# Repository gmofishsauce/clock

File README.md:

# Nixie tube clock with WiFi

This is a Nixie tube clock with IN-12 (axial view) Nixie tubes.
For nice packaging, the design is split into two boards. They
mount [at right angles](https://docs.google.com/presentation/d/11yNopbXGtAtQ4xKlA-b-B579JGvuL5Y8hJCB-doAy8I/edit?usp=sharing) using 96-pin Eurobus ("VME") connectors.

## Subdirectories:

- logic: logic (base board) with Arduino, drivers, power supply.
- display: display board with Nixie tube sockets
- proto: a prototype to check out the PCB footprints.

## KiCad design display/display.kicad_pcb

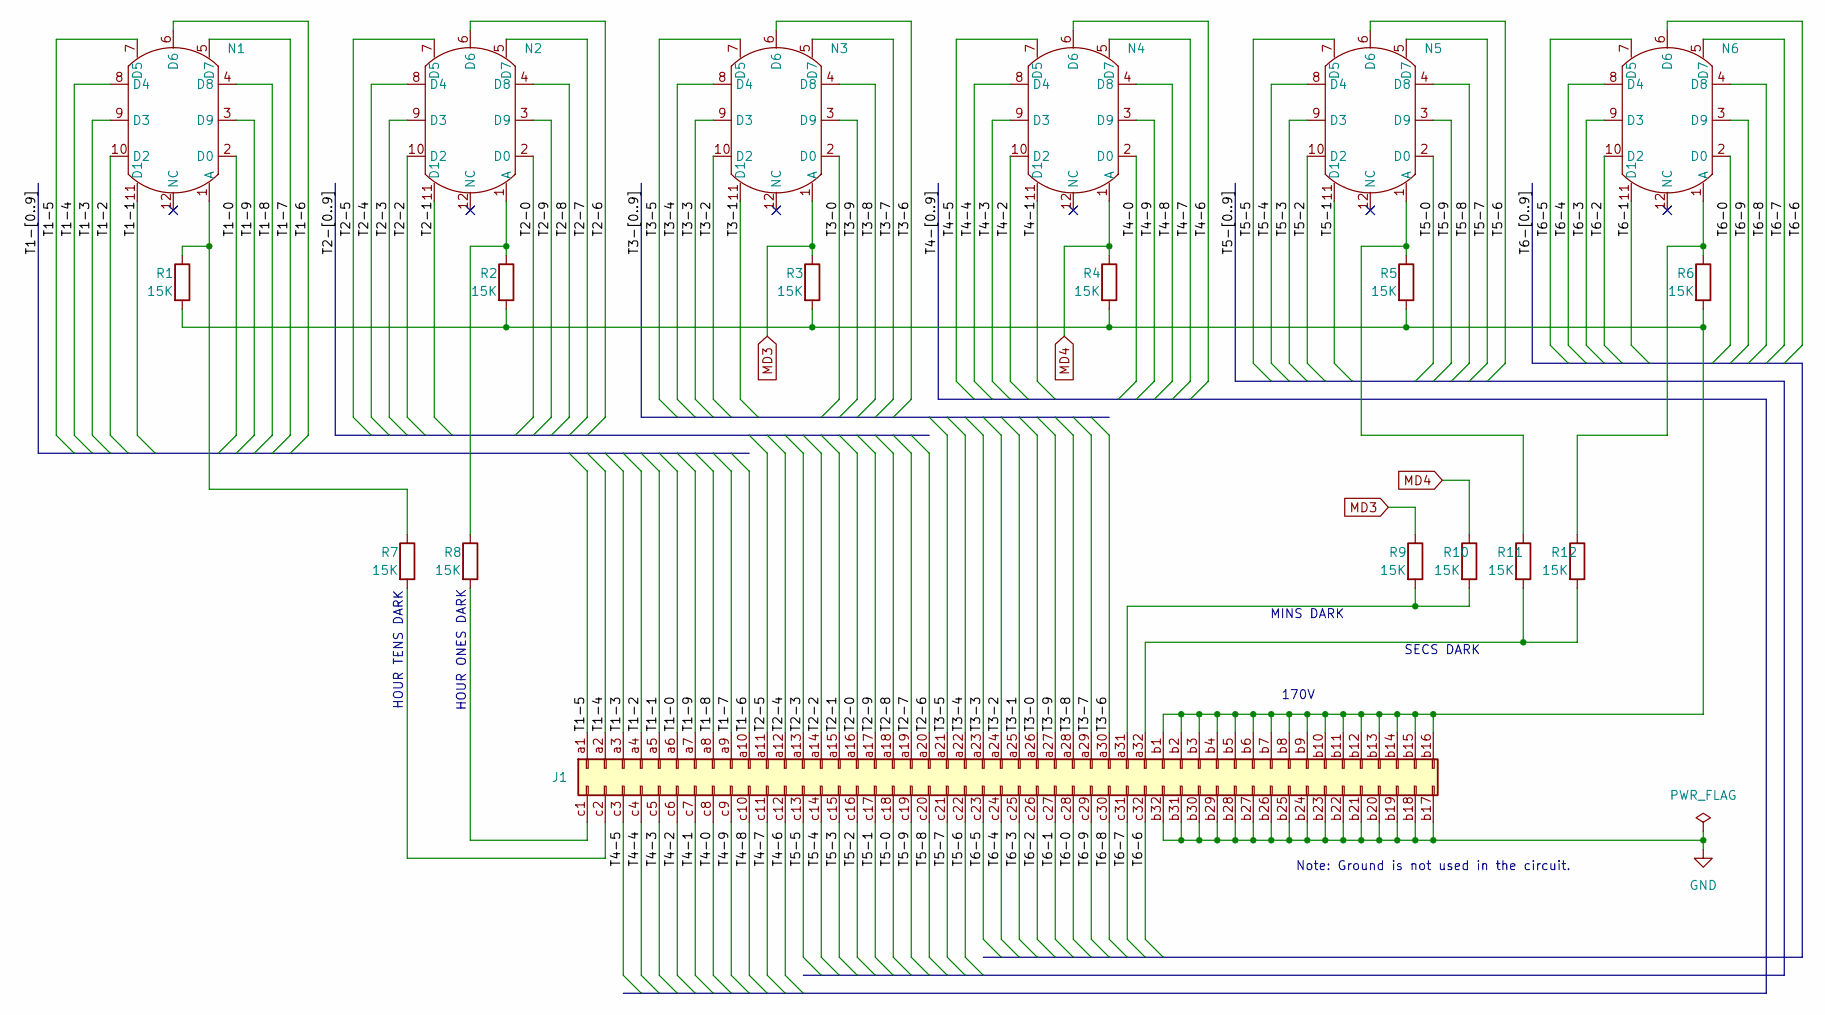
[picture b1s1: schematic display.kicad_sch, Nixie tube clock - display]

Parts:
J1: DIN41612_03x32_ABC; DIN41612_R_3x32_Female_Horizontal_THT
N1, N2, N3, N4, N5, N6: IN_12B_Socket
R1, R2, R3, R4, R5, R6, R7, R8, R9, R10, R11, R12: 15K; R_Box_L13.0mm_W4.0mm_P9.00mm

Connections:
/T1-0: J1.a6, N1.2 (D0)
/T1-1: J1.a5, N1.11 (D1)
/T1-2: J1.a4, N1.10 (D2)
/T1-3: J1.a3, N1.9 (D3)
/T1-4: J1.a2, N1.8 (D4)
/T1-5: J1.a1, N1.7 (D5)
/T1-6: J1.a10, N1.6 (D6)
/T1-7: J1.a9, N1.5 (D7)
/T1-8: J1.a8, N1.4 (D8)
/T1-9: J1.a7, N1.3 (D9)
/T2-0: J1.a16, N2.2 (D0)
/T2-1: J1.a15, N2.11 (D1)
/T2-2: J1.a14, N2.10 (D2)
/T2-3: J1.a13, N2.9 (D3)
/T2-4: J1.a12, N2.8 (D4)
/T2-5: J1.a11, N2.7 (D5)
/T2-6: J1.a20, N2.6 (D6)
/T2-7: J1.a19, N2.5 (D7)
/T2-8: J1.a18, N2.4 (D8)
/T2-9: J1.a17, N2.3 (D9)
/T3-0: J1.a26, N3.2 (D0)
/T3-1: J1.a25, N3.11 (D1)
/T3-2: J1.a24, N3.10 (D2)
/T3-3: J1.a23, N3.9 (D3)
/T3-4: J1.a22, N3.8 (D4)
/T3-5: J1.a21, N3.7 (D5)
/T3-6: J1.a30, N3.6 (D6)
/T3-7: J1.a29, N3.5 (D7)
/T3-8: J1.a28, N3.4 (D8)
/T3-9: J1.a27, N3.3 (D9)
/T4-0: J1.c8, N4.2 (D0)
/T4-1: J1.c7, N4.11 (D1)
/T4-2: J1.c6, N4.10 (D2)
/T4-3: J1.c5, N4.9 (D3)
/T4-4: J1.c4, N4.8 (D4)
/T4-5: J1.c3, N4.7 (D5)
/T4-6: J1.c12, N4.6 (D6)
/T4-7: J1.c11, N4.5 (D7)
/T4-8: J1.c10, N4.4 (D8)
/T4-9: J1.c9, N4.3 (D9)
/T5-0: J1.c18, N5.2 (D0)
/T5-1: J1.c17, N5.11 (D1)
/T5-2: J1.c16, N5.10 (D2)
/T5-3: J1.c15, N5.9 (D3)
/T5-4: J1.c14, N5.8 (D4)
/T5-5: J1.c13, N5.7 (D5)
/T5-6: J1.c22, N5.6 (D6)
/T5-7: J1.c21, N5.5 (D7)
/T5-8: J1.c20, N5.4 (D8)
/T5-9: J1.c19, N5.3 (D9)
/T6-0: J1.c28, N6.2 (D0)
/T6-1: J1.c27, N6.11 (D1)
/T6-2: J1.c26, N6.10 (D2)
/T6-3: J1.c25, N6.9 (D3)
/T6-4: J1.c24, N6.8 (D4)
/T6-5: J1.c23, N6.7 (D5)
/T6-6: J1.c32, N6.6 (D6)
/T6-7: J1.c31, N6.5 (D7)
/T6-8: J1.c30, N6.4 (D8)
/T6-9: J1.c29, N6.3 (D9)
GND: J1.b17, J1.b18, J1.b19, J1.b20, J1.b21, J1.b22, J1.b23, J1.b24, J1.b25, J1.b26, J1.b27, J1.b28, J1.b29, J1.b30, J1.b31, J1.b32
MD3: N3.1 (A), R3.1, R9.1
MD4: N4.1 (A), R4.1, R10.1
unnamed: J1.a31, R9.2, R10.2
unnamed: J1.a32, R11.2, R12.2
unnamed: J1.b1, J1.b2, J1.b3, J1.b4, J1.b5, J1.b6, J1.b7, J1.b8, J1.b9, J1.b10, J1.b11, J1.b12, J1.b13, J1.b14, J1.b15, J1.b16, R1.2, R2.2, R3.2, R4.2, R5.2, R6.2
unnamed: J1.c1, R8.2
unnamed: J1.c2, R7.2
unnamed: N1.1 (A), R1.1, R7.1
unnamed: N2.1 (A), R2.1, R8.1
unnamed: N5.1 (A), R5.1, R11.1
unnamed: N6.1 (A), R6.1, R12.1

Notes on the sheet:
Note: Ground is not used in the circuit.
MINS DARK
SECS DARK
HOUR ONES DARK
170V
HOUR TENS DARK

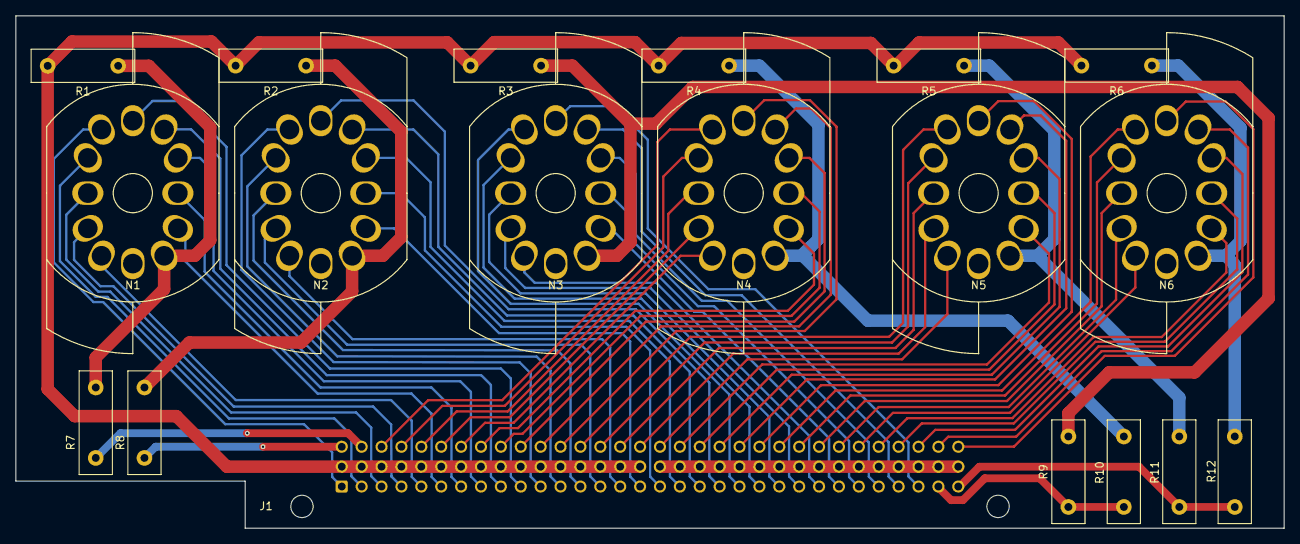
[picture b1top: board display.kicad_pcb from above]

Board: 4 copper layers, 162.0 x 65.4 mm, 19 parts (1 on the bottom side), 72 nets.

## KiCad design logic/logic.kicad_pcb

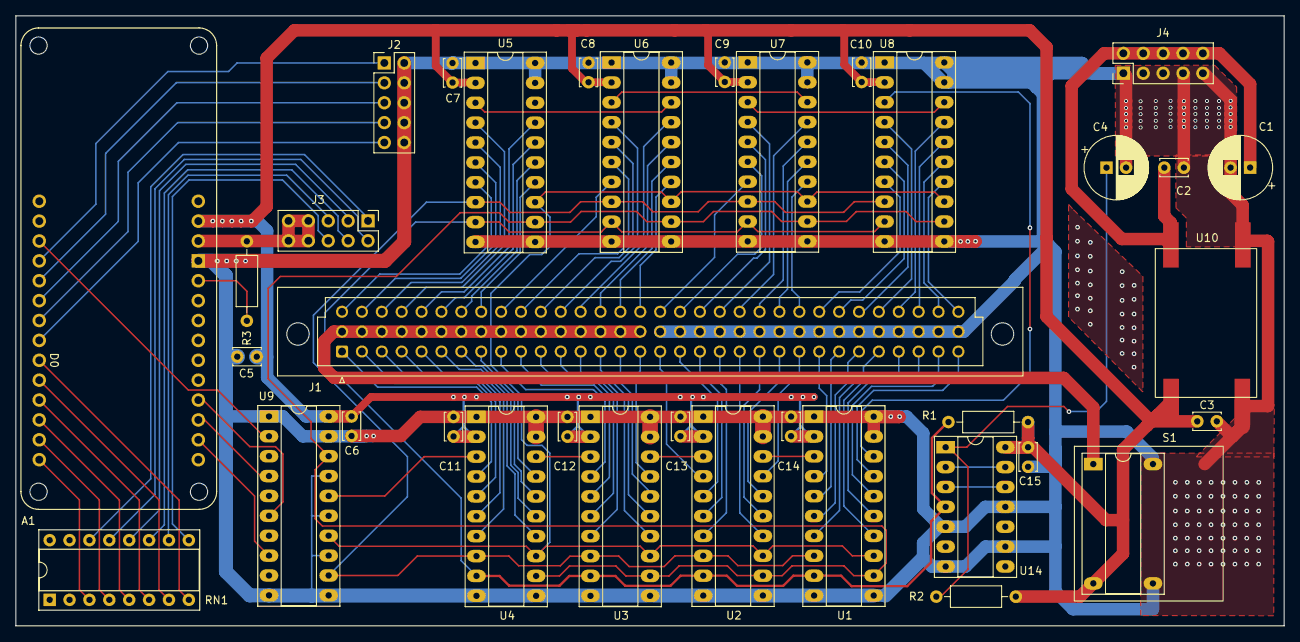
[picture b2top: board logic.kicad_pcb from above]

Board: 4 copper layers, 162.0 x 77.9 mm, 36 parts (0 on the bottom side), 106 nets.

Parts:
A1: Arduino_MKR_WiFi_1010_Socket
C1, C4: C; CP_Radial_D8.0mm_P2.50mm
C2, C3, C5, C6, C7, C8, C9, C10, C11, C12, C13, C14, C15: C; C_Disc_D3.4mm_W2.1mm_P2.50mm
J1: DIN41612_03x32_ABC; DIN41612_R_3x32_Male_Vertical_THT
J2, J3, J4: Conn_02x05_Odd_Even; PinHeader_2x05_P2.54mm_Vertical
R1, R2, R3: R; R_Axial_DIN0207_L6.3mm_D2.5mm_P10.16mm_Horizontal
RN1: R_Pack08; DIP-16_W7.62mm_Socket
S1: NCH8200HV
U1, U2, U3, U4, U5, U6, U7, U8: TPIC6595; DIP-20_W7.62mm_Socket_LongPads
U9: 74HCT244; DIP-20_W7.62mm_Socket_LongPads
U10: TR4R7
U14: 74HC14; DIP-14_W7.62mm_Socket_LongPads

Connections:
/B1-0: J1.a25, U1.4 (DRAIN0)
/B1-1: J1.a26, U1.5 (DRAIN1)
/B1-2: J1.a27, U1.6 (DRAIN2)
/B1-3: J1.a28, U1.7 (DRAIN3)
/B1-4: J1.a29, U1.14 (DRAIN4)
/B1-5: J1.a30, U1.15 (DRAIN5)
/B1-6: J1.a31, U1.16 (DRAIN6)
/B1-7: J1.a32, U1.17 (DRAIN7)
/B2-0: J1.a17, U2.4 (DRAIN0)
/B2-1: J1.a18, U2.5 (DRAIN1)
/B2-2: J1.a19, U2.6 (DRAIN2)
/B2-3: J1.a20, U2.7 (DRAIN3)
/B2-4: J1.a21, U2.14 (DRAIN4)
/B2-5: J1.a22, U2.15 (DRAIN5)
/B2-6: J1.a23, U2.16 (DRAIN6)
/B2-7: J1.a24, U2.17 (DRAIN7)
/B3-0: J1.a9, U3.4 (DRAIN0)
/B3-1: J1.a10, U3.5 (DRAIN1)
/B3-2: J1.a11, U3.6 (DRAIN2)
/B3-3: J1.a12, U3.7 (DRAIN3)
/B3-4: J1.a13, U3.14 (DRAIN4)
/B3-5: J1.a14, U3.15 (DRAIN5)
/B3-6: J1.a15, U3.16 (DRAIN6)
/B3-7: J1.a16, U3.17 (DRAIN7)
/B4-0: J1.a1, U4.4 (DRAIN0)
/B4-1: J1.a2, U4.5 (DRAIN1)
/B4-2: J1.a3, U4.6 (DRAIN2)
/B4-3: J1.a4, U4.7 (DRAIN3)
/B4-4: J1.a5, U4.14 (DRAIN4)
/B4-5: J1.a6, U4.15 (DRAIN5)
/B4-6: J1.a7, U4.16 (DRAIN6)
/B4-7: J1.a8, U4.17 (DRAIN7)
/B5-0: J1.c1, U5.7 (DRAIN3)
/B5-1: J1.c2, U5.6 (DRAIN2)
/B5-2: J1.c3, U5.5 (DRAIN1)
/B5-3: J1.c4, U5.4 (DRAIN0)
/B5-4: J1.c5, U5.17 (DRAIN7)
/B5-5: J1.c6, U5.16 (DRAIN6)
/B5-6: J1.c7, U5.15 (DRAIN5)
/B5-7: J1.c8, U5.14 (DRAIN4)
/B6-0: J1.c9, U6.7 (DRAIN3)
/B6-1: J1.c10, U6.6 (DRAIN2)
/B6-2: J1.c11, U6.5 (DRAIN1)
/B6-3: J1.c12, U6.4 (DRAIN0)
/B6-4: J1.c13, U6.17 (DRAIN7)
/B6-5: J1.c14, U6.16 (DRAIN6)
/B6-6: J1.c15, U6.15 (DRAIN5)
/B6-7: J1.c16, U6.14 (DRAIN4)
/B7-0: J1.c17, U7.7 (DRAIN3)
/B7-1: J1.c18, U7.6 (DRAIN2)
/B7-2: J1.c19, U7.5 (DRAIN1)
/B7-3: J1.c20, U7.4 (DRAIN0)
/B7-4: J1.c21, U7.17 (DRAIN7)
/B7-5: J1.c22, U7.16 (DRAIN6)
/B7-6: J1.c23, U7.15 (DRAIN5)
/B7-7: J1.c24, U7.14 (DRAIN4)
/B8-0: J1.c25, U8.7 (DRAIN3)
/B8-1: J1.c26, U8.6 (DRAIN2)
/B8-2: J1.c27, U8.5 (DRAIN1)
/B8-3: J1.c28, U8.4 (DRAIN0)
/B8-4: J1.c29, U8.17 (DRAIN7)
/B8-5: J1.c30, U8.16 (DRAIN6)
/B8-6: J1.c31, U8.15 (DRAIN5)
/B8-7: J1.c32, U8.14 (DRAIN4)
/RCLK: U1.12 (RCLK), U2.12 (RCLK), U3.12 (RCLK), U4.12 (RCLK), U5.12 (RCLK), U6.12 (RCLK), U7.12 (RCLK), U8.12 (RCLK), U9.18 (O0a)
/SRCK: U1.13 (SRCK), U2.13 (SRCK), U3.13 (SRCK), U4.13 (SRCK), U5.13 (SRCK), U6.13 (SRCK), U7.13 (SRCK), U8.13 (SRCK), U9.14 (O2a)
/Sin1: U1.3 (SER_IN), U2.18 (SER_OUT)
/Sin2: U2.3 (SER_IN), U3.18 (SER_OUT)
/Sin3: U3.3 (SER_IN), U4.18 (SER_OUT)
/Sin4: U4.3 (SER_IN), U9.16 (O1a)
/Sin5: U5.3 (SER_IN), U6.18 (SER_OUT)
/Sin6: U6.3 (SER_IN), U7.18 (SER_OUT)
/Sin7: U7.3 (SER_IN), U8.18 (SER_OUT)
/Sin8: U1.18 (SER_OUT), U8.3 (SER_IN)
/~SRCLR3.3: A1.A1, U9.2 (I0a)
/~SRCLR: U1.8 (~SRCLR), U2.8 (~SRCLR), U3.8 (~SRCLR), U4.8 (~SRCLR), U5.8 (~SRCLR), U6.8 (~SRCLR), U7.8 (~SRCLR), U8.8 (~SRCLR), U9.12 (O3a)
GND: A1.GND, C1.2, C2.2, C3.2, C4.2, C5.2, C6.2, C7.2, C8.2, C9.2, C10.2, C11.2, C12.2, C13.2, C14.2, C15.2, J1.b17, J1.b18, J1.b19, J1.b20, J1.b21, J1.b22, J1.b23, J1.b24, J1.b25, J1.b26, J1.b27, J1.b28, J1.b29, J1.b30, J1.b31, J1.b32, J2.2, J2.4, J2.6, J2.8, J2.10, J4.1, J4.3, J4.5, J4.7, J4.9, S1.3 (LGND), S1.4 (PGND), U1.1 (PGND), U1.10 (PGND), U1.11 (PGND), U1.19 (LGND), U1.20 (PGND), U2.1 (PGND), U2.10 (PGND), U2.11 (PGND), U2.19 (LGND), U2.20 (PGND), U3.1 (PGND), U3.10 (PGND), U3.11 (PGND), U3.19 (LGND), U3.20 (PGND), U4.1 (PGND), U4.10 (PGND), U4.11 (PGND), U4.19 (LGND), U4.20 (PGND), U5.1 (PGND), U5.10 (PGND), U5.11 (PGND), U5.19 (LGND), U5.20 (PGND), U6.1 (PGND), U6.10 (PGND), U6.11 (PGND), U6.19 (LGND), U6.20 (PGND), U7.1 (PGND), U7.10 (PGND), U7.11 (PGND), U7.19 (LGND), U7.20 (PGND), U8.1 (PGND), U8.10 (PGND), U8.11 (PGND), U8.19 (LGND), U8.20 (PGND), U9.1 (OEa), U9.10 (GND), U9.11 (I0b), U9.13 (I1b), U9.15 (I2b), U9.17 (I3b), U9.19 (OEb), U10.3 (GND), U10.4 (IN-), U14.5, U14.7 (GND), U14.9, U14.11
unnamed: A1.D8 (D8_MOSI), U9.4 (I1a)
unnamed: A1.D9 (D9_SCK), U9.6 (I2a)
unnamed: A1.RST (RESET), R3.2
unnamed: C4.1, R2.2, U14.1
unnamed: A1.A2, J2.1
unnamed: A1.A3, J2.3
unnamed: A1.A4, J2.5
unnamed: A1.A5, J2.7
unnamed: A1.A6, J2.9
unnamed: J3.1, RN1.14 (R3.2)
unnamed: J3.2, RN1.13 (R4.2)
unnamed: J3.3, RN1.12 (R5.2)
unnamed: J3.4, RN1.11 (R6.2)
unnamed: J3.5, RN1.10 (R7.2)
unnamed: J3.6, RN1.9 (R8.2)
unnamed: C1.1, C2.1, J4.2, J4.4, J4.6, J4.8, J4.10, U10.1 (IN+)
unnamed: A1.D5, RN1.3 (R3.1)
unnamed: A1.D4, RN1.4 (R4.1)
unnamed: A1.D3, RN1.5 (R5.1)
unnamed: A1.D2, RN1.6 (R6.1)
unnamed: A1.D1, RN1.7 (R7.1)
unnamed: A1.D0, RN1.8 (R8.1)
unnamed: A1.D7, U9.8 (I3a)
unnamed: U14.3, U14.12
unnamed: U14.2, U14.13
POR: R1.2, U1.9 (~G), U2.9 (~G), U3.9 (~G), U4.9 (~G), U5.9 (~G), U6.9 (~G), U7.9 (~G), U8.9 (~G), U14.4
V3.3: A1.3V3 (3.3V), J3.7, J3.8, J3.9, J3.10, R3.1
V5.0: A1.VIN, C3.1, C5.1, C6.1, C7.1, C8.1, C9.1, C10.1, C11.1, C12.1, C13.1, C14.1, C15.1, R1.1, R2.1, S1.2 (LV_IN), U1.2 (VCC), U2.2 (VCC), U3.2 (VCC), U4.2 (VCC), U5.2 (VCC), U6.2 (VCC), U7.2 (VCC), U8.2 (VCC), U9.20 (VCC), U10.2 (5v), U14.14 (VCC)
V170: J1.b1, J1.b2, J1.b3, J1.b4, J1.b5, J1.b6, J1.b7, J1.b8, J1.b9, J1.b10, J1.b11, J1.b12, J1.b13, J1.b14, J1.b15, J1.b16, S1.1 (HV_OUT)

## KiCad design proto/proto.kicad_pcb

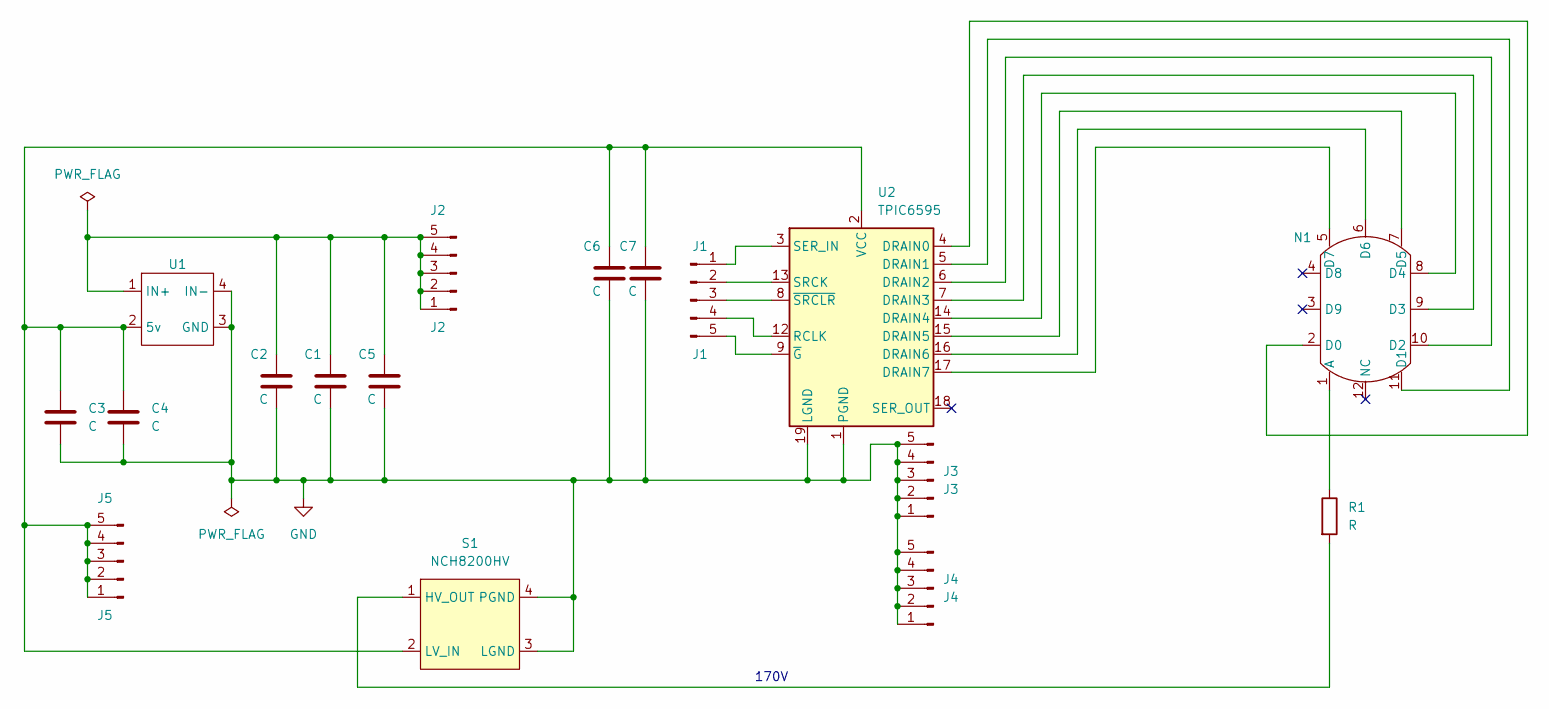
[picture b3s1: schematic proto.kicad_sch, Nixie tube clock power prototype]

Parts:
C1, C3: C; CP_Radial_D5.0mm_P2.50mm
C2, C4, C5, C6, C7: C; C_Disc_D3.0mm_W1.6mm_P2.50mm
J1: J1; PinHeader_1x05_P2.54mm_Vertical_SmallCourt
J2: J2; PinHeader_1x05_P2.54mm_Vertical_SmallCourt
J3: J3; PinHeader_1x05_P2.54mm_Vertical_SmallCourt
J4: J4; PinHeader_1x05_P2.54mm_Vertical_SmallCourt
J5: J5; PinHeader_1x05_P2.54mm_Vertical_SmallCourt
N1: IN_12B_Socket
R1: R; R_Axial_DIN0414_L11.9mm_D4.5mm_P15.24mm_Horizontal
S1: NCH8200HV
U1: TR4R7
U2: TPIC6595; DIP-20_W7.62mm_LongPads

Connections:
GND: C1.2, C2.2, C3.2, C4.2, C5.2, C6.2, C7.2, J3.1, J3.2, J3.3, J3.4, J3.5, J4.1, J4.2, J4.3, J4.4, J4.5, S1.3 (LGND), S1.4 (PGND), U1.3 (GND), U1.4 (IN-), U2.1 (PGND), U2.10 (PGND), U2.11 (PGND), U2.19 (LGND), U2.20 (PGND)
unnamed: J1.1, U2.3 (SER_IN)
unnamed: J1.2, U2.13 (SRCK)
unnamed: J1.3, U2.8 (~SRCLR)
unnamed: J1.4, U2.12 (RCLK)
unnamed: J1.5, U2.9 (~G)
unnamed: C1.1, C2.1, C5.1, J2.1, J2.2, J2.3, J2.4, J2.5, U1.1 (IN+)
unnamed: C3.1, C4.1, C6.1, C7.1, J5.1, J5.2, J5.3, J5.4, J5.5, S1.2 (LV_IN), U1.2 (5v), U2.2 (VCC)
unnamed: N1.1 (A), R1.1
unnamed: N1.2 (D0), U2.4 (DRAIN0)
unnamed: N1.11 (D1), U2.5 (DRAIN1)
unnamed: N1.10 (D2), U2.6 (DRAIN2)
unnamed: N1.9 (D3), U2.7 (DRAIN3)
unnamed: N1.8 (D4), U2.14 (DRAIN4)
unnamed: N1.7 (D5), U2.15 (DRAIN5)
unnamed: N1.6 (D6), U2.16 (DRAIN6)
unnamed: N1.5 (D7), U2.17 (DRAIN7)
unnamed: R1.2, S1.1 (HV_OUT)

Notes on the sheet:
170V

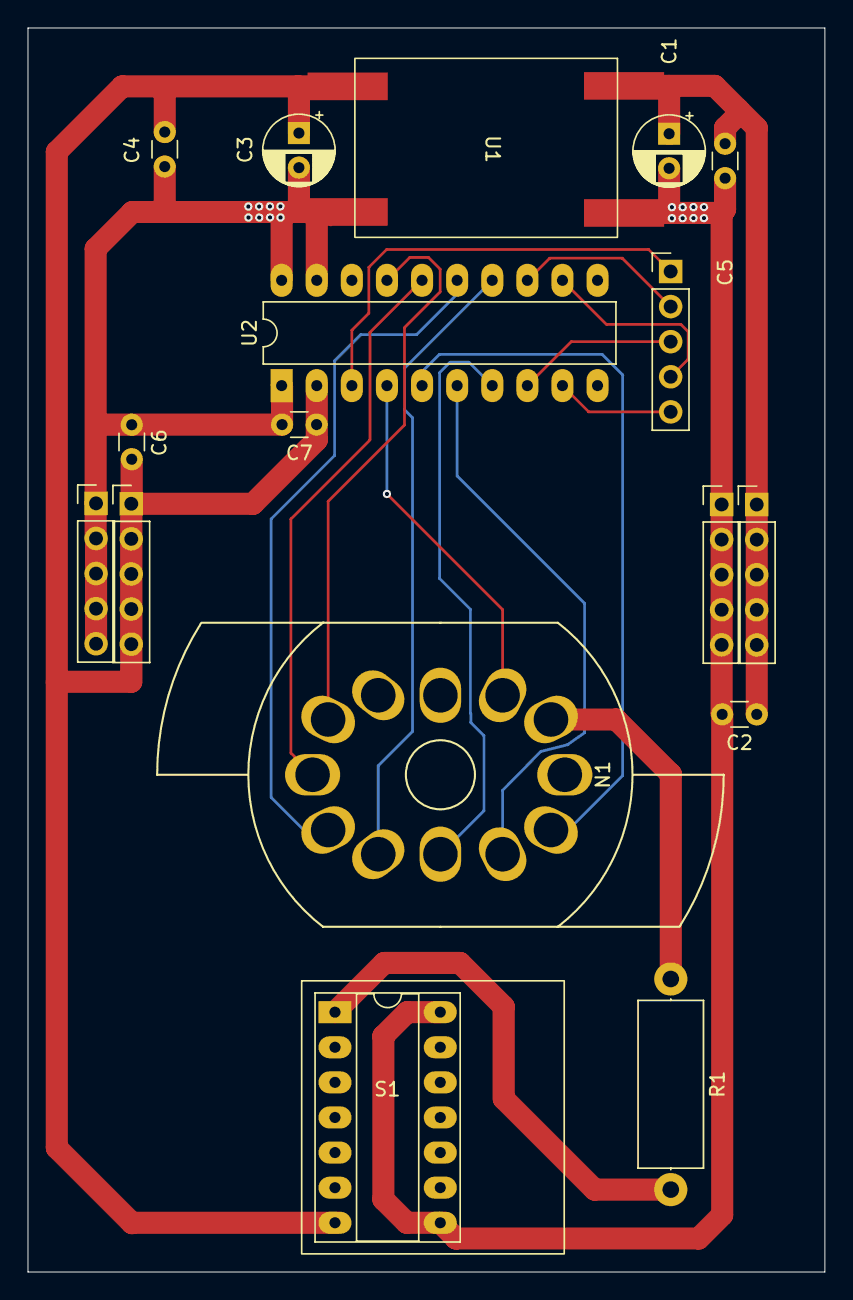
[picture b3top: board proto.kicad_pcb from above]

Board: 4 copper layers, 57.7 x 90.0 mm, 17 parts (0 on the bottom side), 18 nets.

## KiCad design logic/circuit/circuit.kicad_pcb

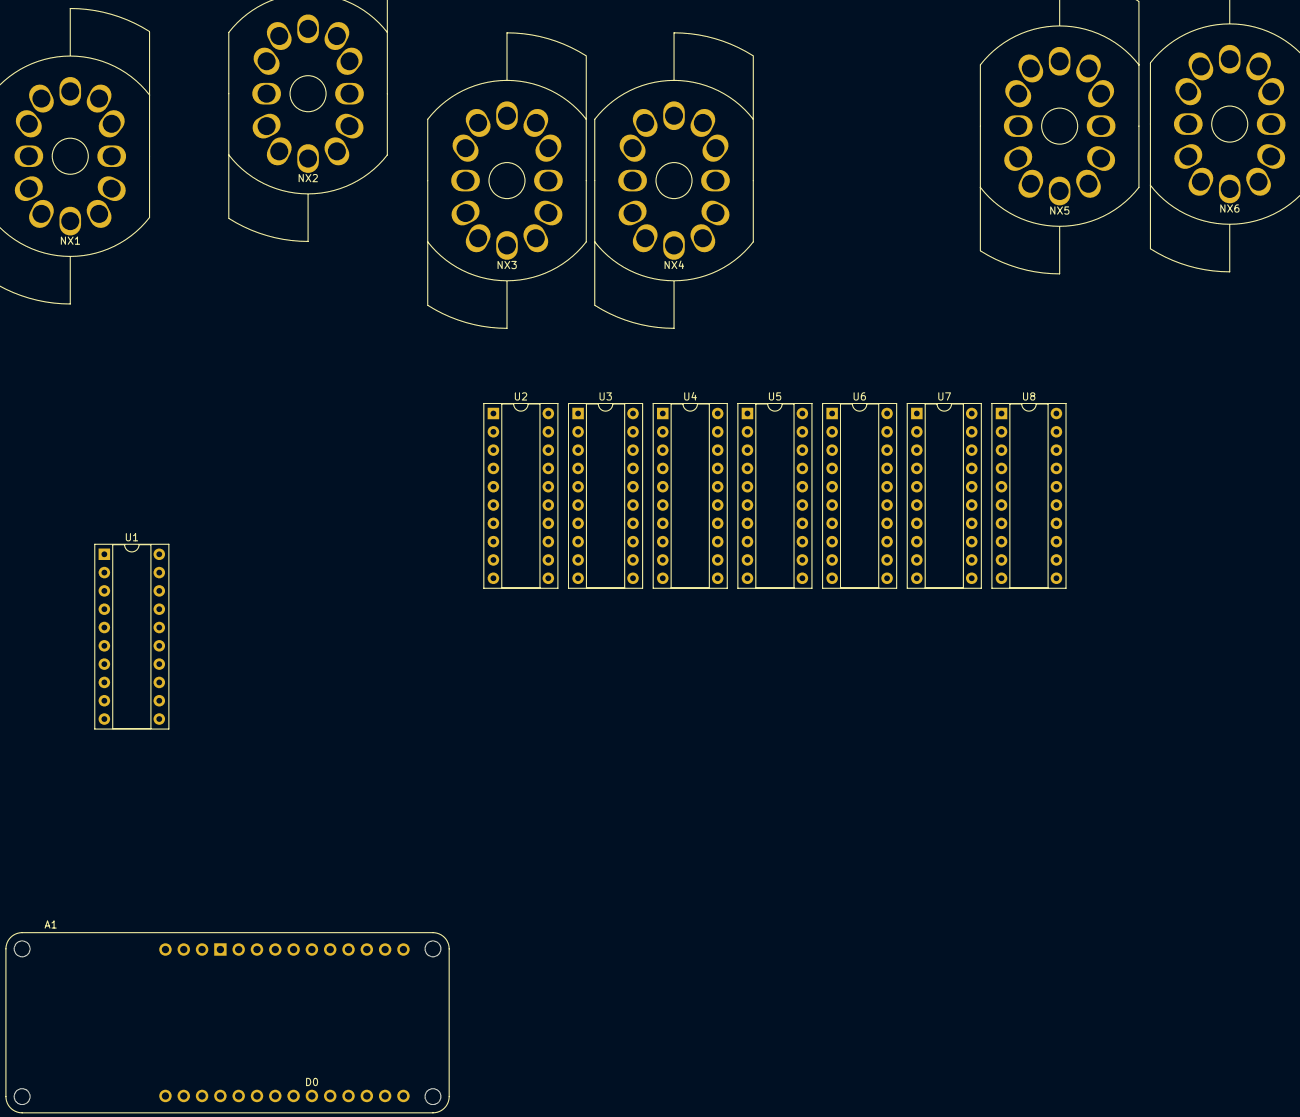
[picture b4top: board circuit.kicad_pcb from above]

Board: 2 copper layers, 15 parts (0 on the bottom side), 15 nets, no tracks yet.

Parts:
A1: Arduino_MKR_WiFi_1010_Socket
NX1, NX2, NX3, NX4, NX5, NX6: IN_12B_Socket
U1, U2, U3, U4, U5, U6, U7, U8: TPIC6595; DIP-20_W7.62mm_Socket

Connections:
/FIX: U5.4 (DRAIN0), U5.17 (DRAIN7), U6.4 (DRAIN0), U6.5 (DRAIN1), U6.6 (DRAIN2), U6.17 (DRAIN7), U7.4 (DRAIN0), U7.5 (DRAIN1), U7.6 (DRAIN2), U7.7 (DRAIN3), U7.14 (DRAIN4), U7.17 (DRAIN7)
COPI: A1.D8 (D8_MOSI), U1.3 (SER_IN)
GND: A1.GND, U1.1 (PGND), U1.10 (PGND), U1.11 (PGND), U1.19 (LGND), U1.20 (PGND), U2.1 (PGND), U2.10 (PGND), U2.11 (PGND), U2.19 (LGND), U2.20 (PGND), U3.1 (PGND), U3.10 (PGND), U3.11 (PGND), U3.19 (LGND), U3.20 (PGND), U4.1 (PGND), U4.10 (PGND), U4.11 (PGND), U4.19 (LGND), U4.20 (PGND), U5.1 (PGND), U5.10 (PGND), U5.11 (PGND), U5.19 (LGND), U5.20 (PGND), U6.1 (PGND), U6.10 (PGND), U6.11 (PGND), U6.19 (LGND), U6.20 (PGND), U7.1 (PGND), U7.10 (PGND), U7.11 (PGND), U7.19 (LGND), U7.20 (PGND), U8.1 (PGND), U8.10 (PGND), U8.11 (PGND), U8.19 (LGND), U8.20 (PGND)
HIGH: U2.8 (~SRCLR), U3.8 (~SRCLR), U4.8 (~SRCLR), U5.8 (~SRCLR), U6.8 (~SRCLR), U7.8 (~SRCLR), U8.8 (~SRCLR)
unnamed: U1.18 (SER_OUT), U2.3 (SER_IN)
unnamed: U2.18 (SER_OUT), U3.3 (SER_IN)
unnamed: U3.18 (SER_OUT), U4.3 (SER_IN)
unnamed: U4.18 (SER_OUT), U5.3 (SER_IN)
unnamed: U5.18 (SER_OUT), U6.3 (SER_IN)
unnamed: U6.18 (SER_OUT), U7.3 (SER_IN)
unnamed: U7.18 (SER_OUT), U8.3 (SER_IN)
RCLK: A1.D7, U1.12 (RCLK), U2.12 (RCLK), U3.12 (RCLK), U4.12 (RCLK), U5.12 (RCLK), U6.12 (RCLK), U7.12 (RCLK), U8.12 (RCLK)
SCLK: A1.D9 (D9_SCK), U1.13 (SRCK), U2.13 (SRCK), U3.13 (SRCK), U4.13 (SRCK), U5.13 (SRCK), U6.13 (SRCK), U7.13 (SRCK), U8.13 (SRCK)
VCC: A1.VIN, U1.2 (VCC), U2.2 (VCC), U3.2 (VCC), U4.2 (VCC), U5.2 (VCC), U6.2 (VCC), U7.2 (VCC), U8.2 (VCC)
~POR: U1.9 (~G), U2.9 (~G), U3.9 (~G), U4.9 (~G), U5.9 (~G), U6.9 (~G), U7.9 (~G), U8.9 (~G)

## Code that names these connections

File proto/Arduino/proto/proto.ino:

#define COPI      8
#define SRCK      9
#define RCLK      A1
#define SRCLR     7

void clearSR() {
  Serial.println("SHIFT REGISTER CLEARED");
  digitalWrite(SRCLR, 0);
  digitalWrite(SRCLR, 1);
}

void clockSR() {
  digitalWrite(SRCK, 0);
  digitalWrite(SRCK, 1);
}

void clockRegister() {
  digitalWrite(RCLK, 0);
  digitalWrite(RCLK, 1);
}

void clockBit(int state) {
  digitalWrite(COPI, state);
  clockSR();
}

void setDefaults() {
  digitalWrite(SRCK, 1);
  digitalWrite(RCLK, 1);
  clearSR();
}

void printMillis(void) {
  long t = millis();
  printMillis(t);
}

void printMillis(long t) {
  char buffer[64];
  (void) sprintf(buffer, "running %ld", t);
  Serial.println(buffer);
}

void setup() {
  Serial.begin(115200);
  while (!Serial) {
    ;
  }
  Serial.println("start: ");
  printMillis();

  pinMode(RCLK, OUTPUT);
  pinMode(COPI, OUTPUT);
  pinMode(SRCK, OUTPUT);
  pinMode(SRCLR, OUTPUT);
  setDefaults();
}

byte buf[8];

#define B1  3
#define B2  2
#define B3  1
#define B4  0
#define B8  4
#define B7  5
#define B6  6
#define B5  7

#define BIT(n) (1<<n)

// Everything is MSB first. The argument is a byte stored in an int.
void byteOut(int b) {
  for (int i = 0; i < 8; ++i) {
    int state = ((b << i) & 0x80) ? HIGH : LOW;
    clockBit(state);
  }
}

void bufOut(byte *pb) {
  for (int i = 0; i < 8; ++i, ++pb) {
    byteOut(*pb);
  }
  clockRegister();
}

void loop() {
  for(;;) {
    printMillis();

    for(int i = 0; i < 8; ++i) { buf[i] = 0x00; }
    bufOut(buf);
    Serial.println("All bits off, including darkener bits");
    delay(8000);

    // FACT: B1-7 turns on the "9" filament in the seconds' units.
    // B1-6 turns on the "8" filament.
    for(int i = 0; i < 8; ++i) { buf[i] = 0x00; }
    buf[B1] = BIT(6);
    bufOut(buf);
    Serial.println("One filament lit in seconds tube");
    delay(8000);

    for(int i = 0; i < 8; ++i) { buf[i] = 0x00; }
    buf[B8] = 0x81;
    bufOut(buf);
    Serial.println("Seconds darkener enabled");
    delay(8000);
  }
}

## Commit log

2024-12-19 Initial commit. Schematic partially complete.
2024-12-20 Commit obsolete version before major revision
2024-12-23 Temporary commit of circuit/ which will end up on Gitlab.
2025-01-04 Change to new 96-pin DIN-41612 schematic symbol in custom library
2025-01-05 Complete schematic. No DRC errors. Place components on PCB.
2025-01-05 Add footprint for HV supply to NixComp library and schematic.
2025-01-08 Some changes to logic board. Begin schematic for display board.
2025-01-08 Complete rev 1 (alpha) schematics. Both pass DRC.
2025-01-08 Assign footprints for display and create PCB design
2025-01-11 Layout is ongoing
2025-01-11 Add footprint for NCH8200 high voltage supply
2025-01-11 Update schematic and PCB with HV supply footprint
2025-01-13 Additional minor tweaking
2025-01-29 LEDs connected by 10-pin connector now. 96 pin connector simplified.
2025-01-30 Add low voltage supply to logic board
2025-02-02 Finally figure out how to attach nets to the NCH8200.
2025-02-11 Clean up symbol library references to be local to repo
2025-02-21 Commit older work
2025-02-21 Symbol libraries are correct now (I think)
2025-02-21 Fix a problem with R1 on PCB
2025-02-21 Add Nixie socket to NixComp lib and update PCB
2025-02-21 Update libraries, schematic, and layout with buck converter
2025-02-21 Start prototype
2025-02-23 Ongoing development of prototype, symbols, footprints, and logic schematic
2025-02-25 Add footprint for socketed HV supply. Add R1 which was forgotten. Revise layout for significantly better density.
2025-02-26 Ongoing development
2025-02-26 Improve footprint for pin connectors and align four power and ground connectors (I hope)
2025-02-26 Ongoing development. Add ground vias.
2025-02-27 Equivalent of code complete on the proto board
2025-02-27 Completely revise high voltage converter footprint and circuit du to previous errors. Generate Gerbers. Some issues remain.
2025-03-08 Review and regenerate Gerbers.
2025-03-29 Prototype development in progress
2025-03-29 Prototype works now
2025-03-30 Non-working SPI library code
2025-03-31 Commit changes from yesterday's working session with Dan.
2025-04-08 Begin incorporating feedback from prototype. Checkpoint.
2025-04-09 Complete schematic and begin logic board layout.
2025-04-10 Ongoing development. Add shunt resistors to display board.
2025-04-18 Proposed final display board positioning
2025-04-18 Ongoing layout work on logic board.
2025-04-19 Tenatively, all parts in final positions
2025-04-19 Schematic corrected and display board is partially routed
2025-04-20 Display board is completely routed
2025-04-20 Minor corrections and evaluate DRC warnings
2025-04-20 Minor cleanups and generate fabrication outputs (Gerbers)
2025-04-20 Improve 3D model for prototype fab purposes
2025-04-21 Ongoing development - logic board routing
2025-04-21 Ongoing development of logic board.
2025-04-22 Logic board is mostly routed. Changes to schematic for routing.
2025-04-22 Routing is complete. Validation and checking begins.
2025-04-22 DRC warnings evaluated
2025-04-23 Minor fussing and run DRC. Generate Gerbers and drill files.
2025-04-23 Enlage notch in display board and minor fussing. New Gerbers.
2025-06-03 Update Arduino test code to clock boards and plot display schematic as a PDF.
2025-06-08 Update simple bit bang test
